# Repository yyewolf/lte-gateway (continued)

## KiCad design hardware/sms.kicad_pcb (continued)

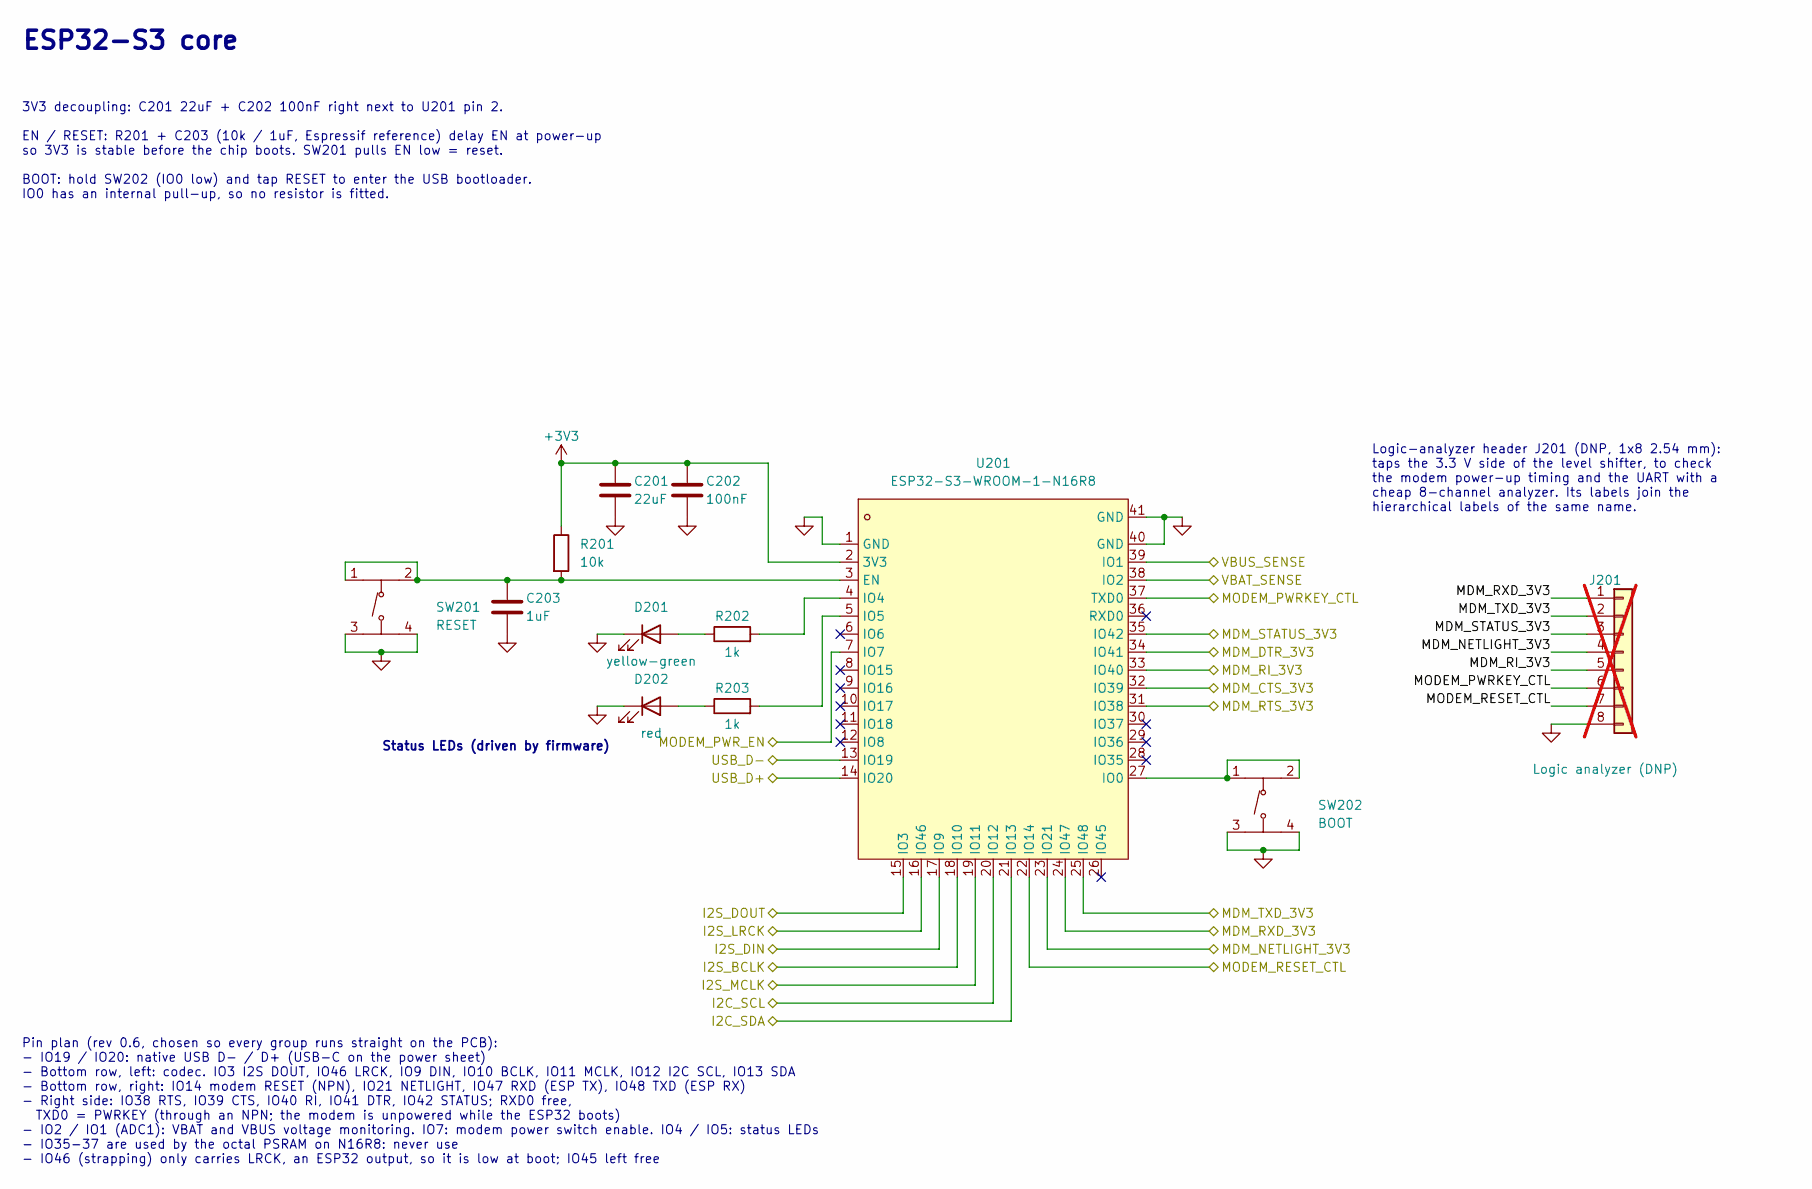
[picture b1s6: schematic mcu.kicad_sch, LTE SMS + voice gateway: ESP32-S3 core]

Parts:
C201: 22uF; C_0805_2012Metric; MPN CL21A226MAQNNNE; LCSC Part C45783
C202: 100nF; C_0402_1005Metric; MPN CL05B104KO5NNNC; LCSC Part C1525
C203: 1uF; C_0402_1005Metric; MPN CL05A105KA5NQNC; LCSC Part C52923
D201: yellow-green; LED_0603_1608Metric; MPN KT-0603YG; LCSC Part C2289
D202: red; LED_0603_1608Metric; MPN KT-0603R; LCSC Part C2286
J201: Logic analyzer (DNP); PinHeader_1x08_P2.54mm_Vertical; not fitted
R201: 10k; R_0402_1005Metric; MPN 0402WGF1002TCE; LCSC Part C25744
R202, R203: 1k; R_0402_1005Metric; MPN 0402WGF1001TCE; LCSC Part C11702
SW201: RESET; SW-SMD_4P-L5.1-W5.1-P3.70-LS6.5-TL_H1.5; MPN TS-1187A-B-A-B; LCSC Part C318884
SW202: BOOT; SW-SMD_4P-L5.1-W5.1-P3.70-LS6.5-TL_H1.5; MPN TS-1187A-B-A-B; LCSC Part C318884
U201: ESP32-S3-WROOM-1-N16R8; WIRELM-SMD_ESP32-S3-WROOM-1; MPN ESP32-S3-WROOM-1-N16R8; LCSC Part C2913202

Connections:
+3V3: C201.1, C202.1, R201.1, U201.2 (3V3); also elsewhere on the board
/Audio/I2C_SCL: U201.20 (IO12); also elsewhere on the board
/Audio/I2C_SDA: U201.21 (IO13); also elsewhere on the board
/Audio/I2S_BCLK: U201.18 (IO10); also elsewhere on the board
/Audio/I2S_DIN: U201.17 (IO9); also elsewhere on the board
/Audio/I2S_DOUT: U201.15 (IO3); also elsewhere on the board
/Audio/I2S_LRCK: U201.16 (IO46); also elsewhere on the board
/Audio/I2S_MCLK: U201.19 (IO11); also elsewhere on the board
/ESP32-S3/MDM_CTS_3V3: U201.32 (IO39); also elsewhere on the board
/ESP32-S3/MDM_DTR_3V3: U201.34 (IO41); also elsewhere on the board
/ESP32-S3/MDM_NETLIGHT_3V3: J201.4, U201.23 (IO21); also elsewhere on the board
/ESP32-S3/MDM_RI_3V3: J201.5, U201.33 (IO40); also elsewhere on the board
/ESP32-S3/MDM_RTS_3V3: U201.31 (IO38); also elsewhere on the board
/ESP32-S3/MDM_RXD_3V3: J201.1, U201.24 (IO47); also elsewhere on the board
/ESP32-S3/MDM_STATUS_3V3: J201.3, U201.35 (IO42); also elsewhere on the board
/ESP32-S3/MDM_TXD_3V3: J201.2, U201.25 (IO48); also elsewhere on the board
/ESP32-S3/MODEM_PWRKEY_CTL: J201.6, U201.37 (TXD0); also elsewhere on the board
/ESP32-S3/MODEM_RESET_CTL: J201.7, U201.22 (IO14); also elsewhere on the board
/ESP32-S3/USB_D+: U201.14 (IO20); also elsewhere on the board
/ESP32-S3/USB_D-: U201.13 (IO19); also elsewhere on the board
/ESP32-S3/VBAT_SENSE: U201.38 (IO2); also elsewhere on the board
/ESP32-S3/VBUS_SENSE: U201.39 (IO1); also elsewhere on the board
/Power & USB/MODEM_PWR_EN: U201.7 (IO7); also elsewhere on the board
GND: C201.2, C202.2, C203.2, D201.1 (K), D202.1 (K), J201.8, SW201.3 (C), SW201.4 (D), SW202.3 (C), SW202.4 (D), U201.1 (GND), U201.40 (GND), U201.41 (GND); also elsewhere on the board
unnamed: D201.2 (A), R202.1
unnamed: D202.2 (A), R203.1
unnamed: C203.1, R201.2, SW201.1 (A), SW201.2 (B), U201.3 (EN)
unnamed: SW202.1 (A), SW202.2 (B), U201.27 (IO0)
unnamed: R202.2, U201.4 (IO4)
unnamed: R203.2, U201.5 (IO5)

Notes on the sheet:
ESP32-S3 core
3V3 decoupling: C201 22uF + C202 100nF right next to U201 pin 2. EN / RESET: R201 + C203 (10k / 1uF, Espressif reference) delay EN at power-up so 3V3 is stable before the chip boots. SW201 pulls EN low = reset. BOOT: hold SW202 (IO0 low) and tap RESET to enter the USB bootloader. IO0 has an interna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
Logic-analyzer header J201 (DNP, 1x8 2.54 mm): taps the 3.3 V side of the level shifter, to check the modem power-up timing and the UART with a cheap 8-channel analyzer. Its labels join the hierarchical labels of the same name.
Status LEDs (driven by firmware)
Pin plan (rev 0.6, chosen so every group runs straight on the PCB): - IO19 / IO20: native USB D- / D+ (USB-C on the power sheet) - Bottom row, left: codec. IO3 I2S DOUT, IO46 LRCK, IO9 DIN, IO10 BCLK, IO11 MCLK, IO12 I2C SCL, IO13 SDA - Bottom row, right: IO14 modem RESET (NPN), IO21 NETLIGHT, IO47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

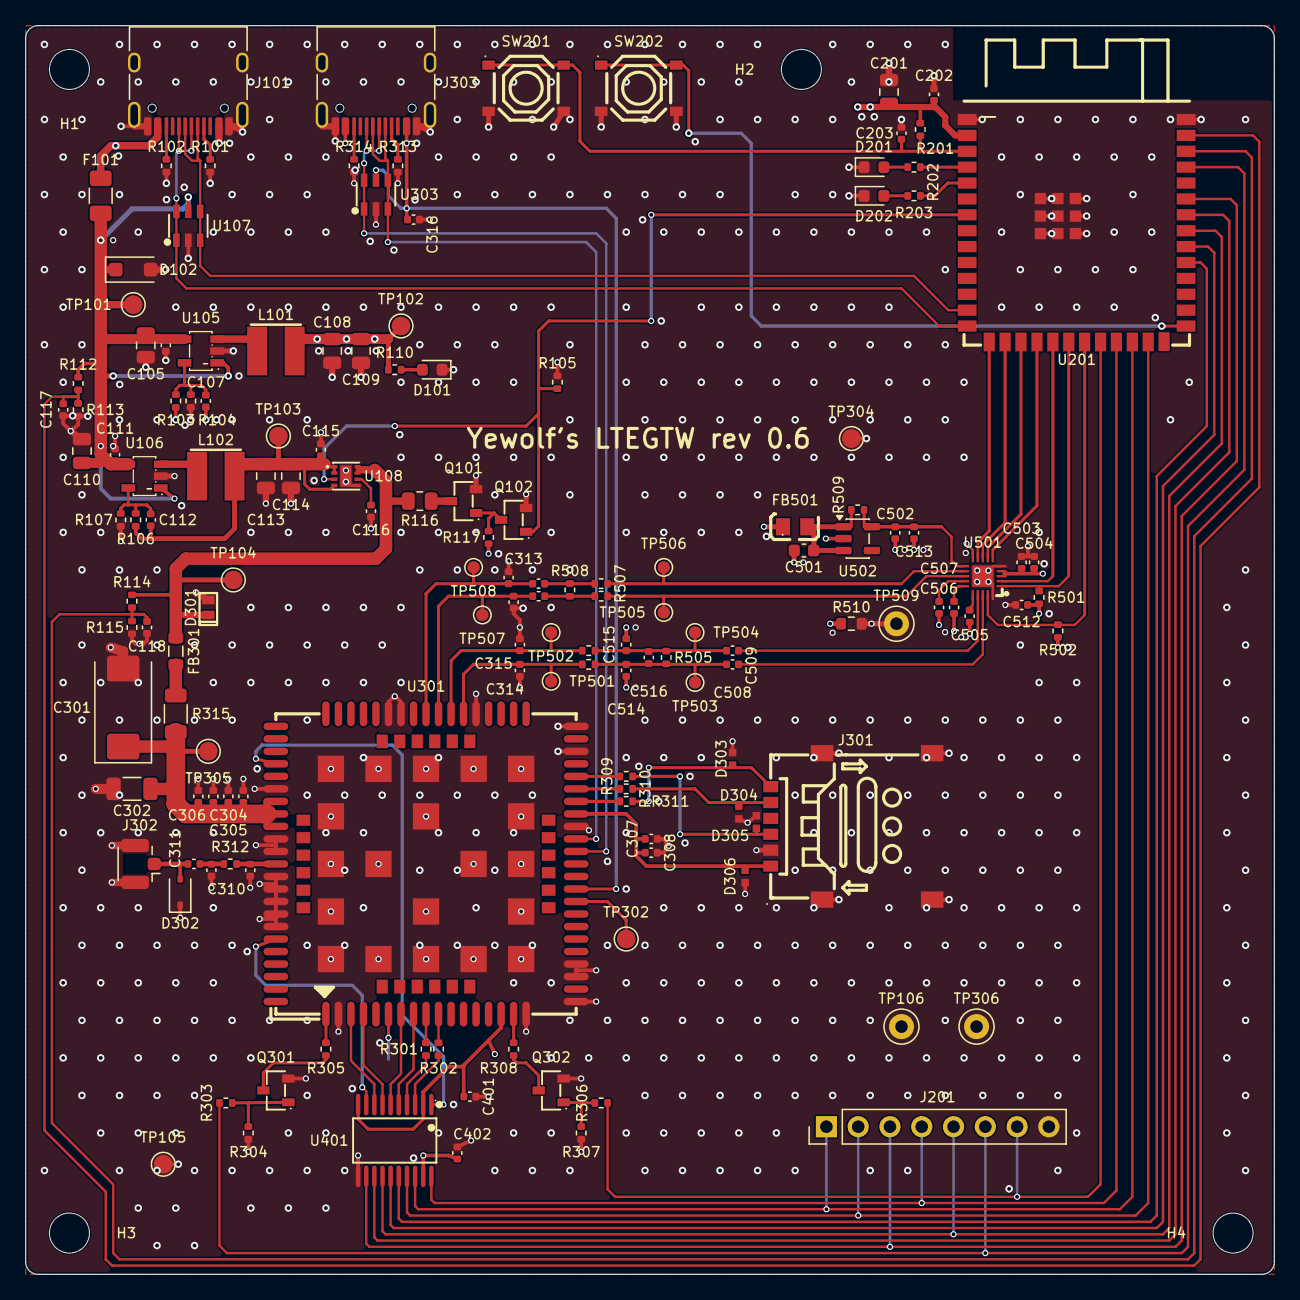
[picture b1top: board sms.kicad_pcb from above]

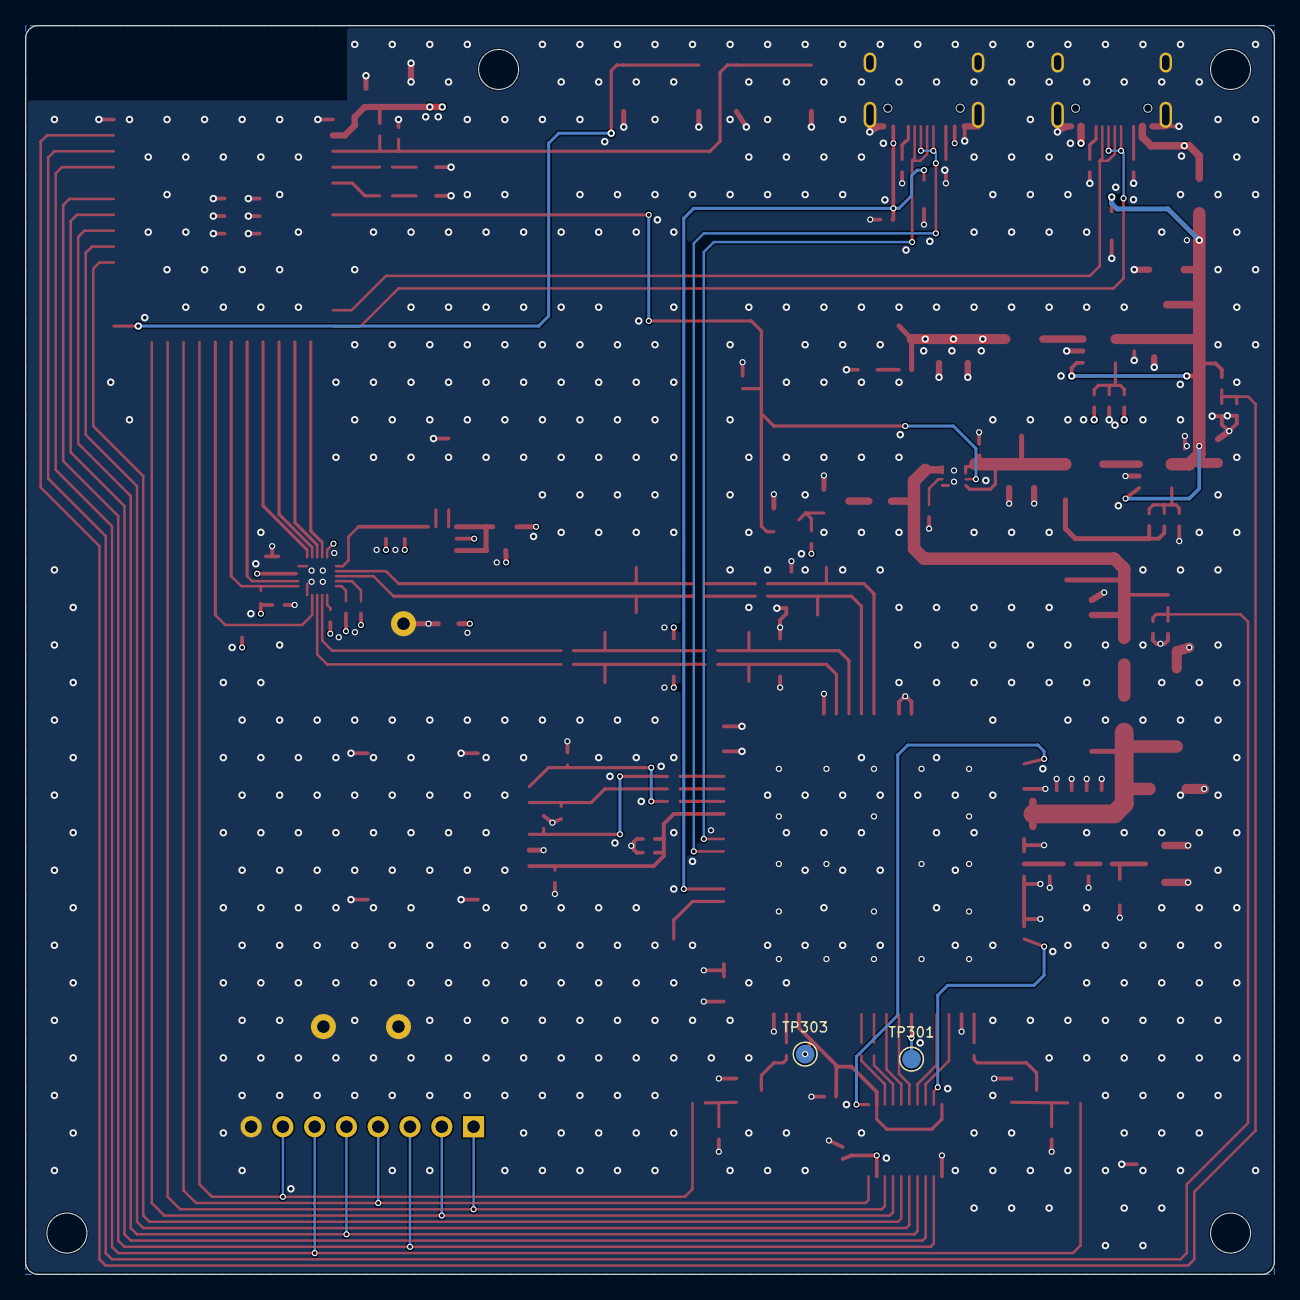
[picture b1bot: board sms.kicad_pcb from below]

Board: 4 copper layers, 99.8 x 99.8 mm, 154 parts (2 on the bottom side), 98 nets.

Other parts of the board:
H1, H2, H3, H4: M3; MountingHole_3.2mm_M3

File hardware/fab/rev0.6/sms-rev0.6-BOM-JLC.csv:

Comment,Designator,Footprint,JLCPCB Part #
100R@100MHz,FB501,L0805,C1015
1k,"R110,R202,R203,R305,R308",R_0402_1005Metric,C11702
TPS22965DSGR,U108,UDFN-8_L2.0-W2.0-P0.50-TL-EP,C122837
100uF,C302,C_1206_3216Metric,C15008
10nF,C116,C_0402_1005Metric,C15195
100nF,"C106,C111,C117,C118,C202,C304,C307,C316,C401,C402,C502,C503,C504",C_0402_1005Metric,C1525
100pF,C311,C_0402_1005Metric,C1546
22pF,"C107,C112",C_0402_1005Metric,C1555
33pF,"C305,C308,C312,C313,C314,C315",C_0402_1005Metric,C1562
USB-C (power + ESP32 USB),"J101,J303",USB_C_Receptacle_HRO_TYPE-C-31-M-12,C165948
2.2uH,"L101,L102",IND-SMD_L4.0-W4.0_FNR40XXS,C167869
30R@100MHz 4A,FB301,L_0805_2012Metric,C16903
0R,"R312,R509",R_0402_1005Metric,C17168
TXS0108EPWR,U401,TSSOP-20_L6.5-W4.4-P0.65-LS6.4-BL,C17206
22R,R116,R_0805_2012Metric,C17561
0R,R315,R_1206_3216Metric,C17888
SMF5.0A,D102,D_SOD-123F,C193402
10uF,C501,C_0603_1608Metric,C19702
MMBT3904,"Q301,Q302",SOT-23-3_L2.9-W1.3-P1.90-LS2.4-BR,C20526
AO3400A,Q101,SOT-23-3_L2.9-W1.3-P1.90-LS2.4-BR,C20917
2A hold,F101,Fuse_1206_3216Metric,C20988
0R,R510,R_0603_1608Metric,C21189
red,D202,LED_0603_1608Metric,C2286
yellow-green,"D101,D201",LED_0603_1608Metric,C2289
100R,"R301,R302",R_0402_1005Metric,C25076
220R,R508,R_0402_1005Metric,C25091
22R,"R309,R310,R311",R_0402_1005Metric,C25092
100k,"R103,R105,R112,R114,R115,R117",R_0402_1005Metric,C25741
10k,"R201,R503,R504,R506,R507",R_0402_1005Metric,C25744
160k,R106,R_0402_1005Metric,C25757
22k,R104,R_0402_1005Metric,C25768
30k,R107,R_0402_1005Metric,C25776
47k,"R113,R304,R307",R_0402_1005Metric,C25792
2.2k,"R501,R502,R505",R_0402_1005Metric,C25879
4.7k,"R303,R306",R_0402_1005Metric,C25900
5.1k,"R101,R102,R313,R314",R_0402_1005Metric,C25905
ESP32-S3-WROOM-1-N16R8,U201,WIRELM-SMD_ESP32-S3-WROOM-1,C2913202
ESD56301D05,D301,DFN1610-2L_L1.6-W1.0-P1.10-RD,C2939837
Nano-SIM holder,J301,SIM-SMD_C77877,C2963104
RESET,"SW201,SW202",SW-SMD_4P-L5.1-W5.1-P3.70-LS6.5-TL_H1.5,C318884
10pF,C306,C_0402_1005Metric,C32949
22uF,"C105,C108,C109,C110,C113,C114,C201",C_0805_2012Metric,C45783
TPD1E10B06,"D303,D304,D305,D306",X1SON-2_L1.0-W0.6-P0.65-BI-1,C48260
1uF,"C115,C203,C303,C505,C506,C507,C508,C509,C510,C511,C512",C_0402_1005Metric,C52923
A7670E-LASE,U301,LGA-124_L24.0-W24.0-P1.0-A7670C-LASS,C5362211
USBLC6-2SC6,"U107,U303",SOT-23-6_L2.9-W1.6-P0.95-LS2.8-BL,C7519
SY8089AAAC,"U105,U106",SOT-23-5_L3.0-W1.7-P0.95-LS2.8-BR,C78988
220uF,C301,CP_EIA-7343-31_Kemet-D,C8024
2N7002,Q102,SOT-23-3_L2.9-W1.3-P1.90-LS2.4-BR,C8545
u.FL,J302,U.FL_Hirose_U.FL-R-SMT-1_Vertical,C88374
ES8311,U501,WQFN-20_L3.0-W3.0-P0.40-BL-EP1.7,C962342

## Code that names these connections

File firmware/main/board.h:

// Pin map of the LTE SMS gateway rev0.6 (read from the rev0.6 Gerber netlist).
#pragma once
#include <stdbool.h>

// Modem control (through NPN transistors / load switch)
#define PIN_MODEM_PWR_EN   7    // high = modem supply (U108) on; R105 pulls it low at reset
#define PIN_MODEM_PWRKEY   43   // high = PWRKEY pressed (Q301). Also the ROM's UART0 TX at boot.
#define PIN_MODEM_RESET    14   // high = RESET held (Q302). Never together with PWRKEY.
#define PIN_MODEM_STATUS   42   // input, high = modem running
#define PIN_MODEM_NETLIGHT 21
#define PIN_MODEM_RI       40
#define PIN_MODEM_DTR      41   // keep low

// UART to the modem, through the TXS0108E level shifter
#define MODEM_UART         UART_NUM_1
#define PIN_MODEM_TX       47   // ESP32 TX -> modem RXD
#define PIN_MODEM_RX       48   // ESP32 RX <- modem TXD
#define MODEM_BAUD         115200

// LEDs (high = on)
#define PIN_LED_GREEN      4
#define PIN_LED_RED        5

// BOOT button (SW202), low = pressed. Hold 5 s while running = setup mode.
#define PIN_BOOT_BUTTON    0

// ES8311 codec
#define PIN_I2C_SCL        12
#define PIN_I2C_SDA        13
#define PIN_I2S_MCLK       11
#define PIN_I2S_BCLK       10
#define PIN_I2S_LRCK       46
#define PIN_I2S_DOUT       3    // ESP32 -> codec DAC (uplink: what the caller hears)
#define PIN_I2S_DIN        9    // codec ADC -> ESP32 (downlink: the caller's voice)
#define ES8311_I2C_ADDR    0x18

// Supply sense (ADC1)
#define PIN_VBUS_SENSE     1    // x 147/47
#define PIN_VBAT_SENSE     2    // x 2, on +3V8 after the modem switch

#define AUDIO_RATE_HZ      8000 // narrowband, same as G.711

// board.c
void board_early_init(void);   // first thing in app_main: PWRKEY/RESET/PWR_EN low, LEDs off
void board_adc_init(void);
float board_vbus(void);        // volts at the USB input
float board_vbat(void);        // volts on +3V8 after the modem supply switch
void board_led(int pin, bool on);
